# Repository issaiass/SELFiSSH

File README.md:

# SELFiSSH - Solar-Powered Data Acquisition System

<details open>
<summary> <b>Brief Review</b></summary>

**SELFiSSH** (Self-Contained, Low-power, Flexible, Intelligent Sampling and Storage Hardware) is a solar-powered, self-contained data acquisition and logging system designed for environmental monitoring and remote sensing applications. This hardware project includes complete Eagle CAD schematics, PCB board layouts, Gerber manufacturing files, and a comprehensive bill of materials.

The system features an ATmega168 microcontroller running at 11.0592 MHz, integrated solar charging capability with LiPo battery backup, RS-232 serial communication, and innovative daisy-chaining connectors that allow multiple units to be networked together. The power management system uses a BQ24202 charger IC to intelligently manage power from both solar and battery sources.

**Key capabilities:**
- Solar-powered with battery backup (3.7V LiPo)
- Autonomous operation with minimal external infrastructure
- Modular daisy-chain architecture for distributed sensor networks
- Comprehensive power management and conditioning
- Multiple communication interfaces (RS-232, inter-unit daisy-chain)

Below you can see the PCB design visualization:

</details>

<details open>
<summary> <b>Project Structure</b></summary>

The project is organized into several key directories and files:

```
SELFiSSH/
├── SELFiSSH.sch              # Main schematic file (Eagle CAD)
├── SELFiSSH.brd              # PCB board layout file (Eagle CAD)
├── eagle.epf                 # Eagle project settings
│
├── BOM/
│   └── SELFiSSH.bom          # Bill of Materials (component list)
│
├── Gerbers/                  # Manufacturing files for PCB production
│   ├── SELFiSSH.GTL          # Top copper layer
│   ├── SELFiSSH.GBL          # Bottom copper layer
│   ├── SELFiSSH.GTS          # Top solder mask
│   ├── SELFiSSH.GBS          # Bottom solder mask
│   ├── SELFiSSH.GTO          # Top silkscreen
│   ├── SELFiSSH.GBO          # Bottom silkscreen
│   ├── SELFiSSH.GML          # Milling/edge cuts
│   ├── SELFiSSH.dri          # Drill file
│   ├── SELFiSSH.gpi          # Pick and place
│   └── SELFiSSH.TXT          # Manufacturing notes
│
├── eagleUp/                  # 3D renderings and visualizations
│   ├── eagleUp_SELFiSSH_board_top.png
│   ├── eagleUp_SELFiSSH_board_bottom.png
│   ├── eagleUp_SELFiSSH_top_silk.png
│   ├── eagleUp_SELFiSSH_bottom_silk.png
│   ├── SELFiSSH.png
│   └── SEL-FiSSH.skp         # SketchUp 3D model
│
└── [Archived versions]       # SELFiSH.s#*, SELFiSH.b#*, etc.
    # (Previous design iterations managed by Eagle)
```

</details>

<details open>
<summary> <b>Hardware Architecture</b></summary>

### System Overview

SELFiSSH is built around an ATmega168 microcontroller and is designed as a modular, expandable data acquisition platform. The system architecture emphasizes low power consumption, autonomous operation, and network scalability through daisy-chaining.

### Core Components

| Component | Model | Function |
|-----------|-------|----------|
| **Microcontroller** | ATmega168 | 8-bit processing and data acquisition |
| **Oscillator** | 11.0592 MHz Crystal | Timing reference (standard UART baud rate divisor) |
| **Charger IC** | BQ24202 | Solar/battery power management |
| **Communication** | RS-232 Level Shifter | Serial PC interface via DB9 connector |
| **Power Input** | 5.5V Barrel Jack | External DC power option |
| **Solar Input** | 5.5V JST Connector | Solar panel charging |
| **Battery** | 3.7V LiPo (JST) | Primary energy storage |

### Functional Blocks

**Power Management System**
- Solar input regulation (5.5V input via SOLAR connector)
- Battery charging management (BQ24202 charger IC with intelligent priority switching)
- Multiple decoupling capacitors (0.1µF, 1µF, 10µF, 4.7µF) for supply stability
- Ferrite beads filtering for noise suppression
- Battery backup via 3.7V LiPo (BATT connector)

**Communication Interface**
- RS-232 level shifter subcircuit (provides PC connectivity)
- DB9 male connector (standard serial port interface)
- Programmable baud rate selection via DIP switch (IR_BAUD_SEL)
- 2-pin connector for baud rate configuration

**Data Acquisition & Networking**
- CHAIN-IN and CHAIN-OUT connectors (M03 pads, W237-103 devices)
- Supports daisy-chaining architecture for multi-unit deployments
- 3-pin inter-unit communication links

**Design Quality Indicators**
- Distributed power supply filtering (multiple capacitors across different voltage rails)
- Analog signal conditioning (presence of ferrite beads suggests analog sensor integration)
- Professional manufacturing approach (Gerber files, DFM considerations)

</details>

<details open>
<summary> <b>Design Files & Tools</b></summary>

### Primary Design Files

All design files are in **Eagle CAD format** (version 6.2 or compatible):

- **SELFiSSH.sch** - The main schematic containing all electrical connections and component specifications
- **SELFiSSH.brd** - The PCB layout file with component placement, trace routing, and manufacturing specifications

Both files are **XML-based text formats** with the following characteristics:
- Can be version controlled and diffed via Git
- Compatible with programmatic XML parsing for automation
- Long line lengths (up to 426+ characters) - be prepared when viewing

### Manufacturing Output

The **Gerbers/** directory contains industry-standard Gerber files ready for PCB manufacturing:

- **Copper layers**: GTL (top), GBL (bottom) - actual circuit traces
- **Solder mask**: GTS (top), GBS (bottom) - solder resist areas
- **Silkscreen**: GTO (top), GBO (bottom) - component labels and reference designators
- **Milling file** (GML) - PCB edge cuts and outline
- **Drill file** (.dri) - Via and through-hole specifications
- **Pick & place file** (.gpi) - Component locations for assembly automation

### Visualization & Documentation

- **eagleUp/** folder contains 3D renderings of the board design
- **SEL-FiSSH.vsd** - Visio diagram for system architecture documentation
- **SELFiSSH.eup** - EagleUp 3D project file

### Required Tools

| Tool | Purpose | Version |
|------|---------|---------|
| **Eagle CAD** | Schematic and PCB design editing | 6.2+ |
| **Git** | Version control and design history tracking | Any recent version |
| **Gerber Viewer** (optional) | Manufacturing file visualization | Various (gerbv, ViewMaster, etc.) |
| **SketchUp** (optional) | 3D model review (SEL-FiSSH.skp) | 2016+ |

</details>

<details open>
<summary> <b>Working with This Repository</b></summary>

### Viewing the Design

1. **For schematic review**: Open `SELFiSSH.sch` in Eagle CAD to view electrical connections and component values
2. **For board layout**: Open `SELFiSSH.brd` in Eagle CAD to see component placement and routing
3. **For manufacturing files**: View Gerber files using a Gerber viewer (free online viewers available)
4. **For 3D visualization**: Open files in `eagleUp/` folder to see rendered board images, or open `SEL-FiSSH.skp` in SketchUp

### Making Design Changes

#### Updating Schematics
1. Open `SELFiSSH.sch` in Eagle CAD
2. Make electrical modifications as needed
3. Run **ERC** (Electrical Rule Check) to verify circuit integrity
4. Save the file

#### Updating PCB Layout
1. Open `SELFiSSH.brd` in Eagle CAD
2. Modify component placement and/or trace routing
3. Run **DRC** (Design Rule Check) to verify manufacturing compatibility
4. Verify trace widths, clearances, and layer assignments
5. Save the file

#### Generating Manufacturing Files
After layout changes, regenerate Gerber files:
1. In Eagle: **File → CAM Job**
2. Use the provided `.cam` configuration or create new job
3. Target the `Gerbers/` directory for output
4. Verify all required layers are exported:
   - GTL, GBL (copper)
   - GTS, GBS (mask)
   - GTO, GBO (silkscreen)
   - GML (milling)
   - .dri (drill)

#### Updating Bill of Materials
After schematic changes:
1. In Eagle: **File → Export → Partlist**
2. Export as CSV or text format
3. Verify part numbers match component specifications
4. Update `BOM/SELFiSSH.bom` with the new list

#### Version Control Workflow

When making design modifications:

```bash
# Check current status
git status

# Make your changes in Eagle CAD, then stage them
git add SELFiSSH.sch SELFiSSH.brd

# If updating manufacturing files
git add Gerbers/*

# If updating BOM
git add BOM/SELFiSSH.bom

# Create a descriptive commit
git commit -m "Update: [description of changes]"

# Example commits:
# git commit -m "Fix: Corrected voltage divider ratio on sensor input"
# git commit -m "Update: Improved power supply decoupling"
# git commit -m "Refactor: Reorganized communication interface layout"
```

**Note**: Eagle CAD automatically manages design iteration archives (`.s#*`, `.b#*` files). Do not manually edit these - they are snapshots for reference.

</details>

<details open>
<summary> <b>Component Details</b></summary>

### Power Supply Components

- **Charging IC**: BQ24202 (U3) - Solar power management and battery charging
- **Battery Connector**: 3.7V LiPo via JST 2-pin connector (BATT)
- **Solar Connector**: 5.5V input via JST 2-pin connector (SOLAR)
- **External Power**: 5.5x2.1mm barrel jack (J1)

### Decoupling & Filtering

Multiple capacitor values ensure clean power delivery:
- 0.1µF ceramic (high-frequency noise rejection)
- 1µF tantalum/ceramic (mid-frequency filtering)
- 10µF electrolytic (low-frequency bulk storage)
- 4.7µF ceramic (localized supply stabilization)

Ferrite beads on power rails suppress conducted EMI and provide additional filtering.

### Communication Components

- **Connector**: DB9 male (standard RS-232 port)
- **Level Shifter**: Converts 3.3V/5V logic to ±12V RS-232 levels
- **Baud Rate Selection**: DIP switch allows runtime baud rate configuration

### Data Acquisition Connectors

- **Chain-In**: 3-pin M03 connector for daisy-chain input
- **Chain-Out**: 3-pin M03 connector for daisy-chain output
- Supports inter-unit communication and power distribution in networked deployments

### Oscillator

**11.0592 MHz Crystal (Y1)**
- Standard frequency for microcontroller applications
- Enables clean UART baud rate generation
- Common choice for ATmega microcontrollers

</details>

<details open>
<summary> <b>Specifications & Ratings</b></summary>

### Operating Conditions

- **Microcontroller**: ATmega168 (8 MHz nominal, running at 11.0592 MHz with external crystal)
- **Battery Voltage**: 3.7V nominal (LiPo chemistry)
- **Solar Input**: 5.5V maximum
- **External Power**: 5.5V nominal
- **Serial Communication**: RS-232 logic levels (±12V)

### Physical Design

- **PCB Layers**: 2 layers (top and bottom copper)
- **Connector Types**: JST (power), DB9 (serial), M03/W237-103 (daisy-chain)
- **Oscillator**: 11.0592 MHz, crystal-based timing

### Power Management

- **Charger IC**: BQ24202 - Handles solar charging and battery management
- **Priority Logic**: Solar charging when available; automatic battery backup
- **Supply Regulation**: Distributed capacitance for stable 3.3V/5V rails

</details>

<details open>
<summary> <b>Project History & Licensing</b></summary>

**Version**: 1.0 (Current Release)

**Design Timeline**: The project tracks design iterations through Eagle CAD versioning. Previous versions are preserved as snapshots (`.s#*` and `.b#*` files) for reference and revision control.

**Licensing**: This design is released under **Creative Commons License** (as indicated by CC_TEXT labels in the schematic). Refer to the original schematic for specific license terms.

**Design Philosophy**: SELFiSSH represents an open, modular approach to data acquisition hardware, emphasizing:
- Autonomous, solar-powered operation
- Scalability through daisy-chaining
- Accessibility through standard interfaces (RS-232)
- Professional PCB design standards

</details>

<details open>
<summary> <b>Future Development & Improvements</b></summary>

Potential areas for enhancement:

- **Wireless Communication**: Add Bluetooth or LoRaWAN modules for remote data transmission
- **Expanded Sensor Support**: Develop standardized connector interfaces for various sensors
- **Firmware Development**: Create embedded firmware for common data acquisition patterns
- **Advanced Power Management**: Implement MPPT (Maximum Power Point Tracking) for improved solar efficiency
- **Memory Expansion**: Add external flash storage for extended logging capability
- **3G/4G Connectivity**: Integrate cellular modem for cloud data synchronization

</details>

<details open>
<summary> <b>Contributing & Support</b></summary>

This is an open-source hardware project. Contributions are welcome!

### How to Contribute

1. Fork the repository
2. Create a feature branch for your improvements
3. Make your changes to the design files
4. Document your modifications clearly
5. Submit a pull request with a detailed description of changes

### Reporting Issues

If you find design issues, manufacturing problems, or have suggestions for improvement:
- Check existing design archives for historical context
- Document the issue clearly with references to specific components or sections
- Include Eagle schematic/layout screenshots if applicable

### For Questions or Collaboration

This project welcomes collaboration and questions. When working with the design:
- Refer to `CLAUDE.md` for development guidance and best practices
- Consult Eagle CAD documentation for CAM job and manufacturing workflows
- Review the BOM carefully before ordering components
- Verify DRC/ERC rules pass before manufacturing

</details>

<details open>
<summary> <b>License</b></summary>

This project is licensed under the **Creative Commons Attribution-ShareAlike License**. You are free to use, modify, and distribute this design, provided you:
- Give appropriate credit to the original designers
- Share derivative works under the same license

For full license details, see the Creative Commons website: https://creativecommons.org/licenses/by-sa/4.0/

</details>

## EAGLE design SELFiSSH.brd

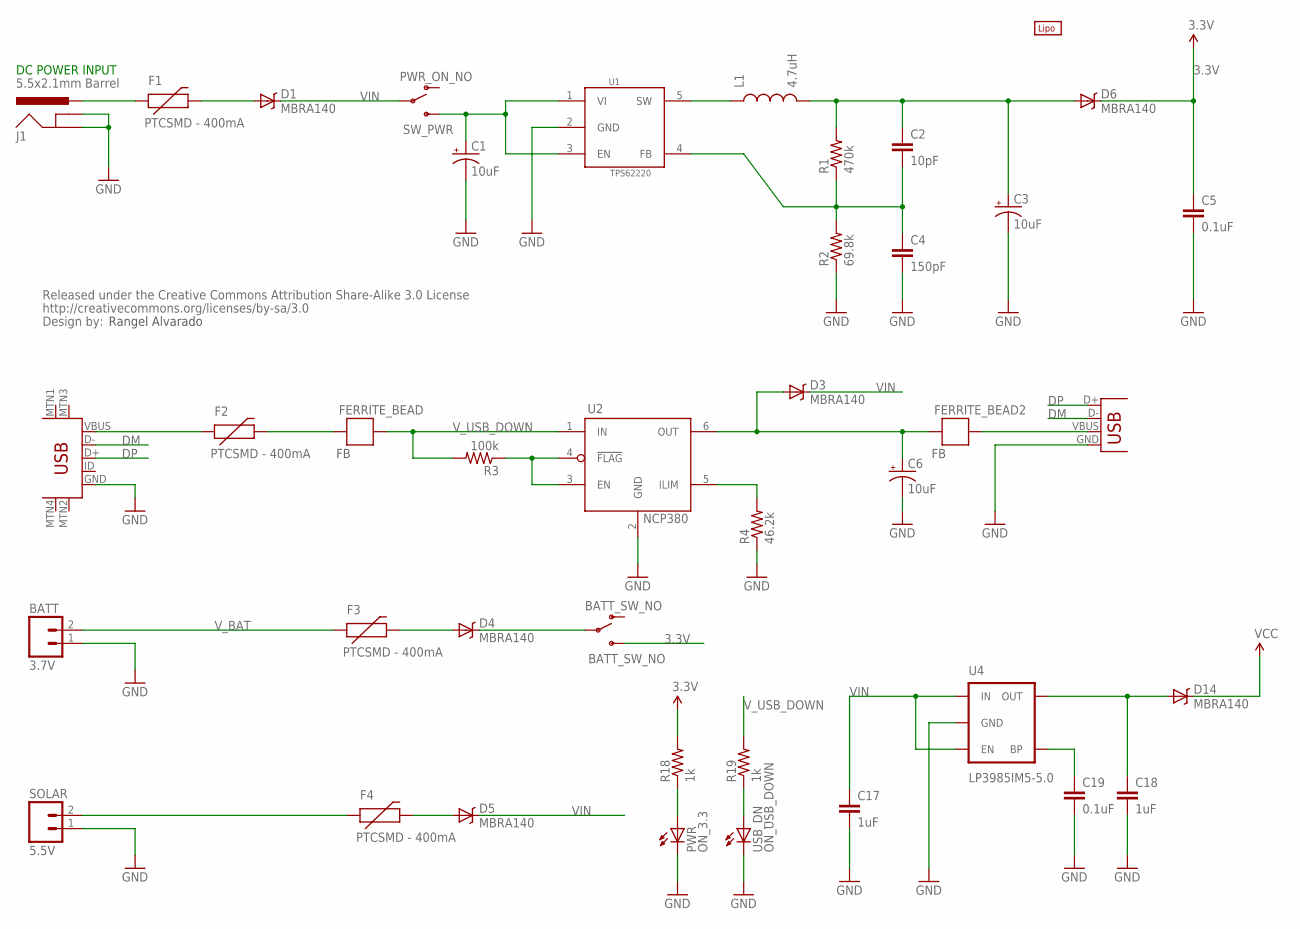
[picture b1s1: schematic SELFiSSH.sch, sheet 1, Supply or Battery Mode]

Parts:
BATT: 3.7V; JST-2-PTH
BATT_SW_NO: BATT_SW_NO; SWITCH-SPDT-SMD
C1, C3, C6: 10uF; EIA3216
C2: 10pF; 0805
C4: 150pF; 0805
C5, C19: 0.1uF; 0805
C17, C18: 1uF; 0805
CC_TEXT1: CREATIVE_COMMONS
D1, D3, D4, D5, D6, D14: MBRA140; SMA-DIODE
F1, F2, F3, F4: PTCSMD - 400mA; PTC-1206
FERRITE_BEAD, FERRITE_BEAD2: FB; 0603
J1: 5.5x2.1mm Barrel; POWER_JACK_SMD
L1: 4.7uH; 0805
PWR: ON_3.3; LED-0603
R1: 470k; 0603-RES
R2: 69.8k; 0603-RES
R3: 100k; 0603-RES
R4: 46.2k; 0603-RES
R18, R19: 1k; 0603-RES
SOLAR: 5.5V; JST-2-PTH
SW_PWR: PWR_ON_NO; SWITCH-SPDT-SMD
U1: TPS62220; TSOT-23-5
U2: NCP380; TSOP6
U4: LP3985IM5-5.0; SOT23-5
U$7: LIPO-OUTLINE1100; LIPO-1100
USB_DN: ON_USB_DOWN; LED-0603
USB_IN: USB_IN; USB-MINIB
USB_OUT: USB_OUT; USB-A-S-SILK-FEMALE

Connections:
3.3V: BATT_SW_NO.3 (S), C5.1, D6.C, R18.2; also elsewhere on the board
DM: USB_IN.D-, USB_OUT.D-
DP: USB_IN.D+, USB_OUT.D+
GND: BATT.1, C1.C (-), C3.C (-), C4.2, C5.2, C6.C (-), C17.2, C18.2, C19.2, J1.GND (GNDBREAK), J1.P$4 (GND), PWR.C, R2.1, R4.1, SOLAR.1, U1.2 (GND), U2.2 (GND), U4.2 (GND), USB_DN.C, USB_IN.GND, USB_OUT.GND; also elsewhere on the board
unnamed: F2.1, USB_IN.VBUS
unnamed: BATT_SW_NO.2, D4.C
unnamed: L1.1, U1.5 (SW)
unnamed: F2.2, FERRITE_BEAD.2
unnamed: C2.1, C3.A (+), D6.A, L1.2, R1.2
unnamed: F1.1, J1.VIN0 (PWR)
unnamed: D1.A, F1.2
unnamed: D4.A, F3.2
unnamed: R3.1, U2.3 (EN), U2.4 (!FLAG)
unnamed: D5.A, F4.2
unnamed: C2.2, C4.1, R1.1, R2.2, U1.4 (FB)
unnamed: R4.2, U2.5 (ILIM)
unnamed: PWR.A, R18.1
unnamed: R19.1, USB_DN.A
unnamed: C6.A (+), D3.A, FERRITE_BEAD2.2, U2.6 (OUT)
unnamed: C1.A (+), SW_PWR.3 (S), U1.1 (VI), U1.3 (EN)
unnamed: C19.1, U4.4 (BP)
unnamed: C18.1, D14.A, U4.5 (OUT)
unnamed: FERRITE_BEAD2.1, USB_OUT.VBUS
SUN: F4.1, SOLAR.2
VCC: D14.C; also elsewhere on the board
VIN: C17.1, D1.C, D3.C, D5.C, SW_PWR.2, U4.1 (IN), U4.3 (EN); also elsewhere on the board
V_BAT: BATT.2, F3.1; also elsewhere on the board
V_USB_DOWN: FERRITE_BEAD.1, R3.2, R19.2, U2.1 (IN)

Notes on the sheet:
DC POWER INPUT
Rangel Alvarado

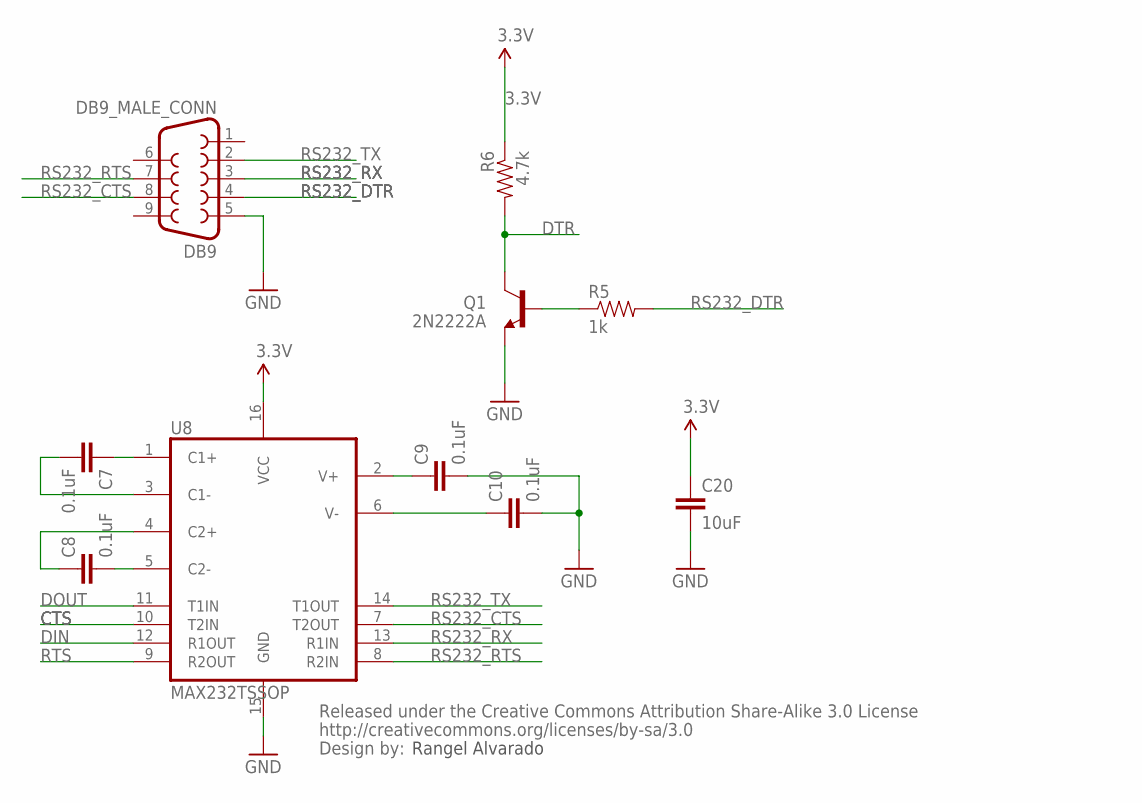
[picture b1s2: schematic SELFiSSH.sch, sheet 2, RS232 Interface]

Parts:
C7, C8, C9, C10: 0.1uF; 0402-CAP
C20: 10uF; 0402-CAP
CC_TEXT2: CREATIVE_COMMONS
DB9_MALE_CONN: DB9; F09HP
Q1: 2N2222A; SOT23-3
R5: 1k; 0402-RES
R6: 4.7k; 0402-RES
U8: MAX232TSSOP; TSSOP16

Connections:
3.3V: C20.1, R6.1, U8.16 (VCC); also elsewhere on the board
CTS: U8.10 (T2IN); also elsewhere on the board
DIN: U8.12 (R1OUT); also elsewhere on the board
DOUT: U8.11 (T1IN); also elsewhere on the board
DTR: Q1.3 (C), R6.2; also elsewhere on the board
GND: C9.2, C10.2, C20.2, DB9_MALE_CONN.5, Q1.2 (E), U8.15 (GND); also elsewhere on the board
unnamed: C9.1, U8.2 (V+)
unnamed: C10.1, U8.6 (V-)
unnamed: C8.2, U8.5 (C2-)
unnamed: C7.2, U8.3 (C1-)
unnamed: C7.1, U8.1 (C1+)
unnamed: C8.1, U8.4 (C2+)
unnamed: Q1.1 (B), R5.1
RS232_CTS: DB9_MALE_CONN.8, U8.7 (T2OUT)
RS232_DTR: DB9_MALE_CONN.4, R5.2
RS232_RTS: DB9_MALE_CONN.7, U8.8 (R2IN)
RS232_RX: DB9_MALE_CONN.3, U8.13 (R1IN)
RS232_TX: DB9_MALE_CONN.2, U8.14 (T1OUT)
RTS: U8.9 (R2OUT); also elsewhere on the board

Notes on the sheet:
Rangel Alvarado

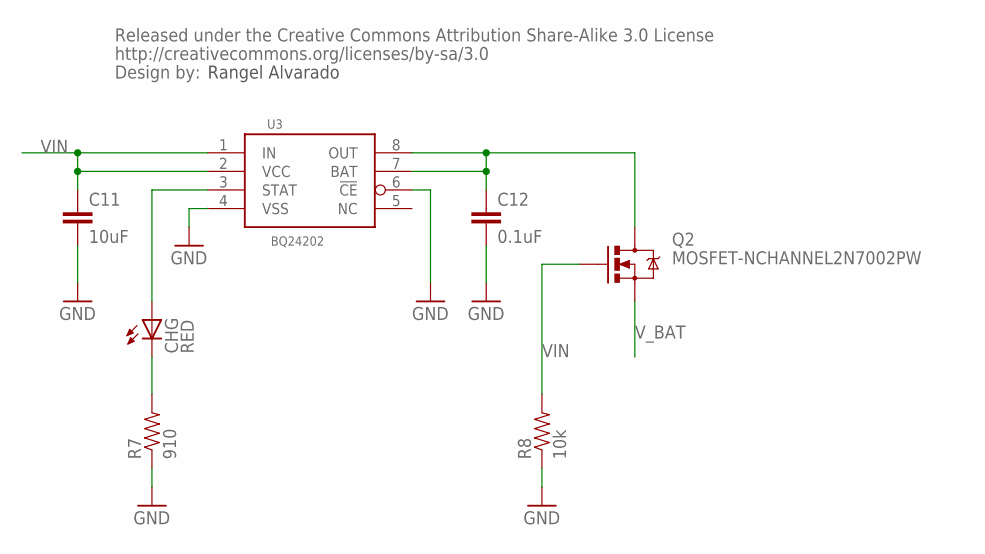
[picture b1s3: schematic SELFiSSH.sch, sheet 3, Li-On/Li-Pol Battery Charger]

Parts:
C11: 10uF; 0805
C12: 0.1uF; 0805
CC_TEXT3: CREATIVE_COMMONS
CHG: RED; LED-1206
Q2: MOSFET-NCHANNEL2N7002PW; SOT323
R7: 910; 0805
R8: 10k; 0805
U3: BQ24202; MSOP-8

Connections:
GND: C11.2, C12.2, R7.1, R8.1, U3.4 (VSS), U3.6 (!CE); also elsewhere on the board
unnamed: CHG.A, U3.3 (STAT)
unnamed: CHG.C, R7.2
unnamed: C12.1, Q2.3 (D), U3.7 (BAT), U3.8 (OUT)
VIN: C11.1, Q2.1 (G), R8.2, U3.1 (IN), U3.2 (VCC); also elsewhere on the board
V_BAT: Q2.2 (S); also elsewhere on the board

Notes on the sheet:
Rangel Alvarado

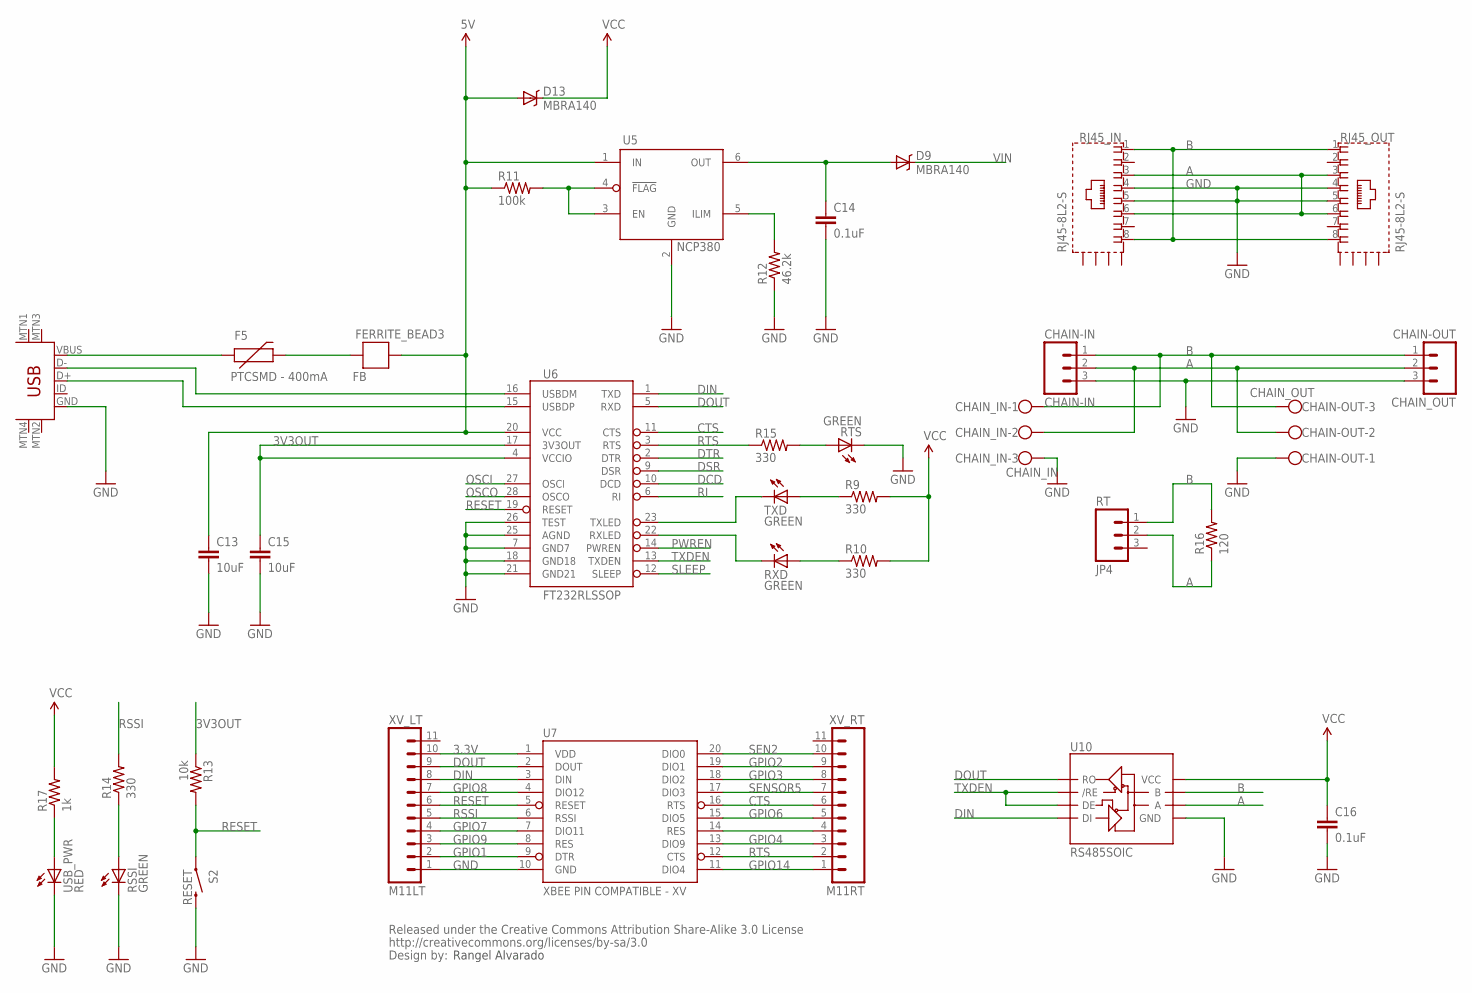
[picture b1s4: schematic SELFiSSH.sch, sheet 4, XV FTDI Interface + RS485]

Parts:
C13, C15: 10uF; 0805
C14, C16: 0.1uF; 0805
CC_TEXT4: CREATIVE_COMMONS
CHAIN-IN: CHAIN-IN; 1X03_LONGPADS
CHAIN-OUT: CHAIN_OUT; W237-103
CHAIN_IN: CHAIN_IN; W237-103
CHAIN_OUT: CHAIN-OUT; 1X03_LONGPADS
D9, D13: MBRA140; SMA-DIODE
F5: PTCSMD - 400mA; PTC-1206
FERRITE_BEAD3: FB; 0603
FTDI: FTDI; USB-MINIB
JP4: RT; 1X03_LONGPADS
R9, R10, R14, R15: 330; 0805
R11: 100k; 0805
R12: 46.2k; 0805
R13: 10k; 0805
R16: 120; 0805
R17: 1k; 0805
RJ45_IN, RJ45_OUT: RJ45-8L2-S; RJ45-SHIELD2
RSSI: GREEN; LED-0603
RTS: GREEN; LED-0603
RXD: GREEN; LED-0603
S2: RESET; TACTILE_SWITCH_TALL
TXD: GREEN; LED-0603
U5: NCP380; TSOP6
U6: FT232RLSSOP; SSOP28DB
U7: XBEE PIN COMPATIBLE - XV; XBEE-SMD
U10: RS485SOIC; SO08
USB_PWR: RED; LED-1206
XV_LT: M11LT; 1X11_LONGPADS
XV_RT: M11RT; 1X11_LONGPADS

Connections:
3.3V: U7.1 (VDD), XV_LT.10; also elsewhere on the board
3V3OUT: C15.1, R13.1, U6.4 (VCCIO), U6.17 (3V3OUT)
5V: C13.1, D13.A, FERRITE_BEAD3.1, R11.1, U5.1 (IN), U6.20 (VCC)
A: CHAIN-IN.2, CHAIN-OUT.2, CHAIN_IN.2, CHAIN_OUT.2, JP4.2, R16.1, RJ45_IN.3, RJ45_IN.6, RJ45_OUT.3, RJ45_OUT.6, U10.6 (A)
B: CHAIN-IN.1, CHAIN-OUT.3, CHAIN_IN.1, CHAIN_OUT.1, JP4.1, R16.2, RJ45_IN.1, RJ45_IN.8, RJ45_OUT.1, RJ45_OUT.8, U10.7 (B)
CTS: U6.11 (CTS), U7.16 (RTS), XV_RT.6; also elsewhere on the board
DCD: U6.10 (DCD)
DIN: U6.1 (TXD), U7.3 (DIN), U10.4 (DI), XV_LT.8; also elsewhere on the board
DOUT: U6.5 (RXD), U7.2 (DOUT), U10.1 (RO), XV_LT.9; also elsewhere on the board
DSR: U6.9 (DSR); also elsewhere on the board
DTR: U6.2 (DTR); also elsewhere on the board
FTDI: FTDI.D+, U6.15 (USBDP)
GND: C13.2, C14.2, C15.2, C16.2, CHAIN-IN.3, CHAIN-OUT.1, CHAIN_IN.3, CHAIN_OUT.3, FTDI.GND, R12.1, RJ45_IN.4, RJ45_IN.5, RJ45_OUT.4, RJ45_OUT.5, RSSI.C, RTS.C, S2.B2 (2), U5.2 (GND), U6.7 (GND7), U6.18 (GND18), U6.21 (GND21), U6.25 (AGND), U6.26 (TEST), U7.10 (GND), U10.5 (GND), USB_PWR.C, XV_LT.1; also elsewhere on the board
GPIO1: U7.9 (DTR), XV_LT.2
GPIO2: U7.19 (DIO1), XV_RT.9
GPIO3: U7.18 (DIO2), XV_RT.8
GPIO4: U7.13 (DIO9), XV_RT.3
GPIO6: U7.15 (DIO5), XV_RT.5
GPIO7: U7.7 (DIO11), XV_LT.4
GPIO8: U7.4 (DIO12), XV_LT.7
GPIO9: U7.8 (RES), XV_LT.3
GPIO14: U7.11 (DIO4), XV_RT.1
unnamed: F5.1, FTDI.VBUS
unnamed: F5.2, FERRITE_BEAD3.2
unnamed: FTDI.D-, U6.16 (USBDM)
unnamed: R15.2, RTS.A
unnamed: RXD.C, U6.22 (RXLED)
unnamed: TXD.C, U6.23 (TXLED)
unnamed: R9.1, TXD.A
unnamed: R10.1, RXD.A
unnamed: C14.1, D9.A, U5.6 (OUT)
unnamed: R14.1, RSSI.A
unnamed: R11.2, U5.3 (EN), U5.4 (!FLAG)
unnamed: R17.1, USB_PWR.A
unnamed: R12.2, U5.5 (ILIM)
unnamed: U7.14 (RES), XV_RT.4
OSCI: U6.27 (OSCI)
OSCO: U6.28 (OSCO)
PWREN: U6.14 (PWREN)
RESET: R13.2, S2.A2 (1), U6.19 (RESET), U7.5 (RESET), XV_LT.6
RI: U6.6 (RI); also elsewhere on the board
RSSI: R14.2, U7.6 (RSSI), XV_LT.5
RTS: R15.1, U6.3 (RTS), U7.12 (CTS), XV_RT.2; also elsewhere on the board
SEN2: U7.20 (DIO0), XV_RT.10
SENSOR5: U7.17 (DIO3), XV_RT.7
SLEEP: U6.12 (SLEEP)
TXDEN: U6.13 (TXDEN), U10.2 (/RE), U10.3 (DE)
VCC: C16.1, D13.C, R9.2, R10.2, R17.2, U10.8 (VCC); also elsewhere on the board
VIN: D9.C; also elsewhere on the board

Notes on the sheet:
Rangel Alvarado

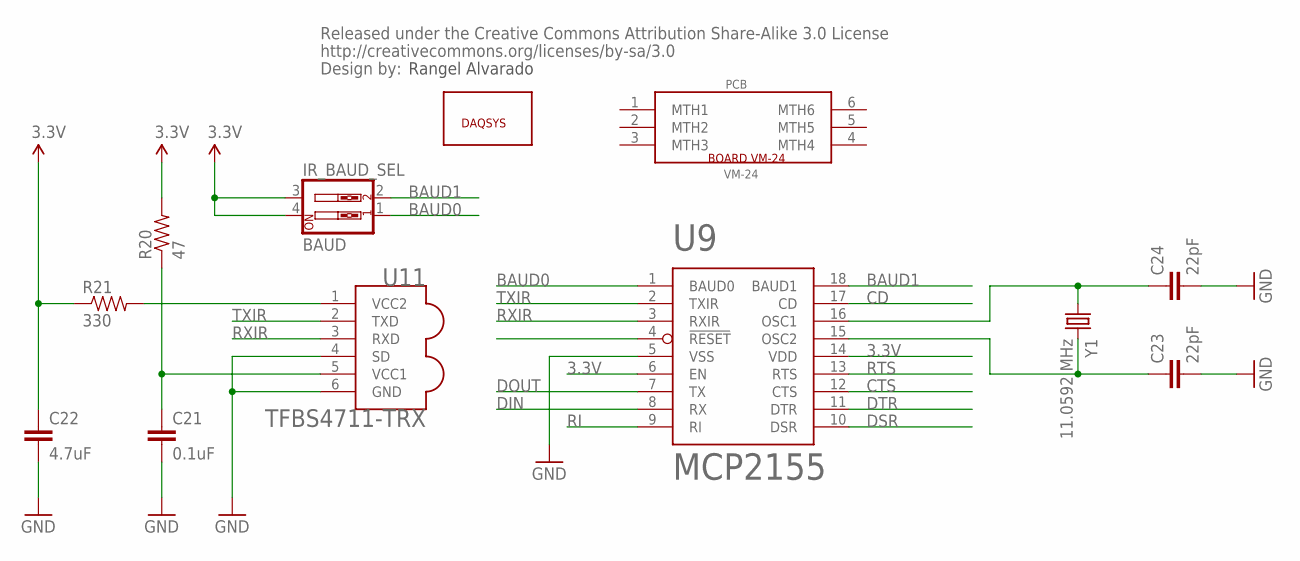
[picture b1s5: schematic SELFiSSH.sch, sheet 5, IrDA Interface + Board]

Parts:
C21: 0.1uF; 0603-CAP
C22: 4.7uF; 0603-CAP
C23, C24: 22pF; 0603-CAP
CC_TEXT5: CREATIVE_COMMONS
IR_BAUD_SEL: BAUD; DIPSWITCH-02
PCB: VM-24
R20: 47; 0603-RES
R21: 330; 0603-RES
U9: MCP2155; SOIC18-W
U11: TFBS4711-TRX; SMD-6
U$1: DAQSYS
Y1: 11.0592 MHz; CRYSTAL-SMD-5X3

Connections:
3.3V: C22.1, IR_BAUD_SEL.3, IR_BAUD_SEL.4, R20.2, R21.1, U9.6 (EN), U9.14 (VDD); also elsewhere on the board
BAUD0: IR_BAUD_SEL.1, U9.1 (BAUD0)
BAUD1: IR_BAUD_SEL.2, U9.18 (BAUD1)
CD: U9.17 (CD)
CTS: U9.12 (CTS); also elsewhere on the board
DIN: U9.8 (RX); also elsewhere on the board
DOUT: U9.7 (TX); also elsewhere on the board
DSR: U9.10 (DSR); also elsewhere on the board
DTR: U9.11 (DTR); also elsewhere on the board
GND: C21.2, C22.2, C23.2, C24.2, U9.5 (VSS), U11.4 (SD), U11.6 (GND); also elsewhere on the board
unnamed: C21.1, R20.1, U11.5 (VCC1)
unnamed: C24.1, U9.16 (OSC1), Y1.1
unnamed: C23.1, U9.15 (OSC2), Y1.3 (2)
unnamed: R21.2, U11.1 (VCC2)
RI: U9.9 (RI); also elsewhere on the board
RTS: U9.13 (RTS); also elsewhere on the board
RXIR: U9.3 (RXIR), U11.3 (RXD)
TXIR: U9.2 (TXIR), U11.2 (TXD)

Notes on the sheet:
Rangel Alvarado

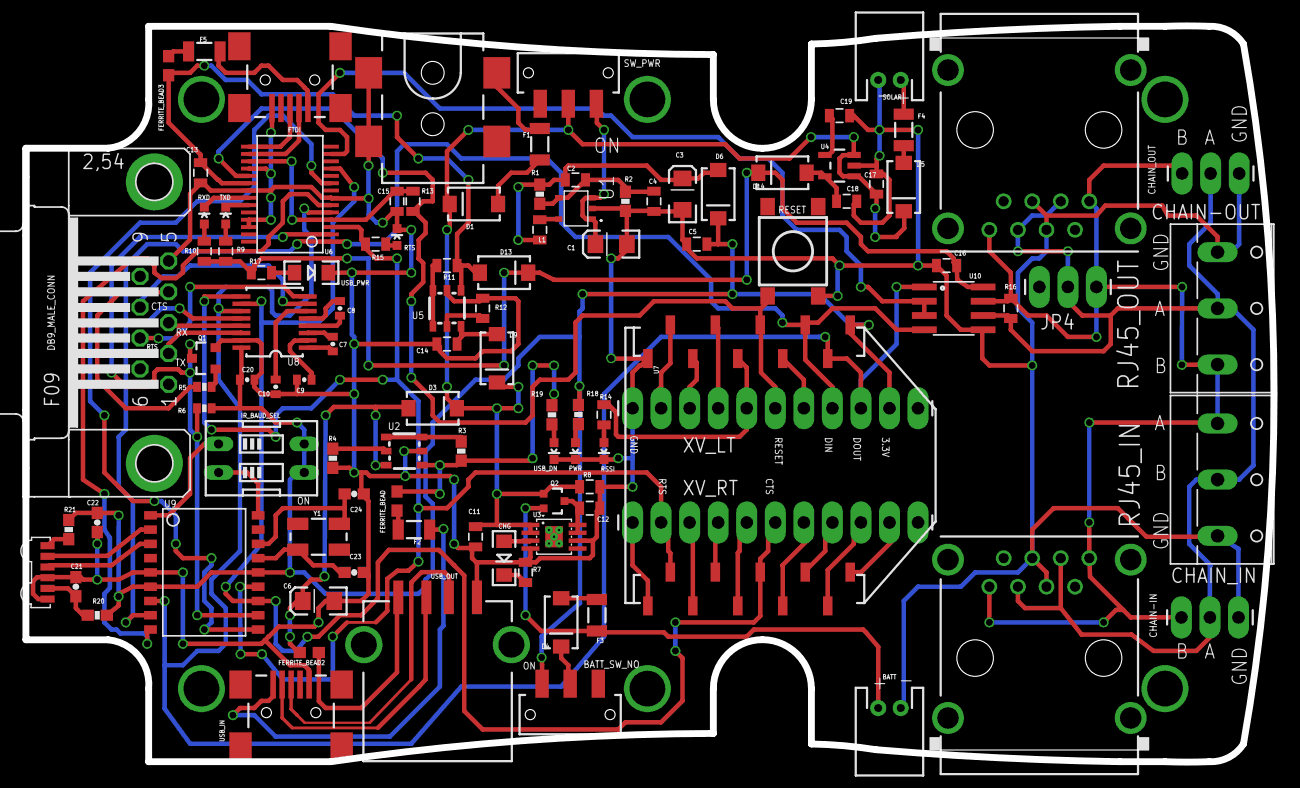
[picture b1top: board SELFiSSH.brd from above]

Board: 2 copper layers, 111.1 x 65.5 mm, 112 parts (1 on the bottom side), 91 nets.

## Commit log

2014-11-01 :octocat: Added .gitattributes & .gitignore files
2014-11-01 SELFiSSH v1.0
    Multiprotocol (Physical Layer) for communication devices
2026-01-20 removed files and adde README.md
2026-01-20 Remove tracked files now in .gitignore
2026-01-20 updated documentation

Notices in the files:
parts and their libraries:
SparkFun-Connectors: Licensing: CC v3.0 Share-Alike You are welcome to use this library for commercial purposes.
SparkFun-Aesthetics: Released under the Creative Commons Attribution Share-Alike 3.0 License
SparkFun-Aesthetics: http://creativecommons.org/licenses/by-sa/3.0
